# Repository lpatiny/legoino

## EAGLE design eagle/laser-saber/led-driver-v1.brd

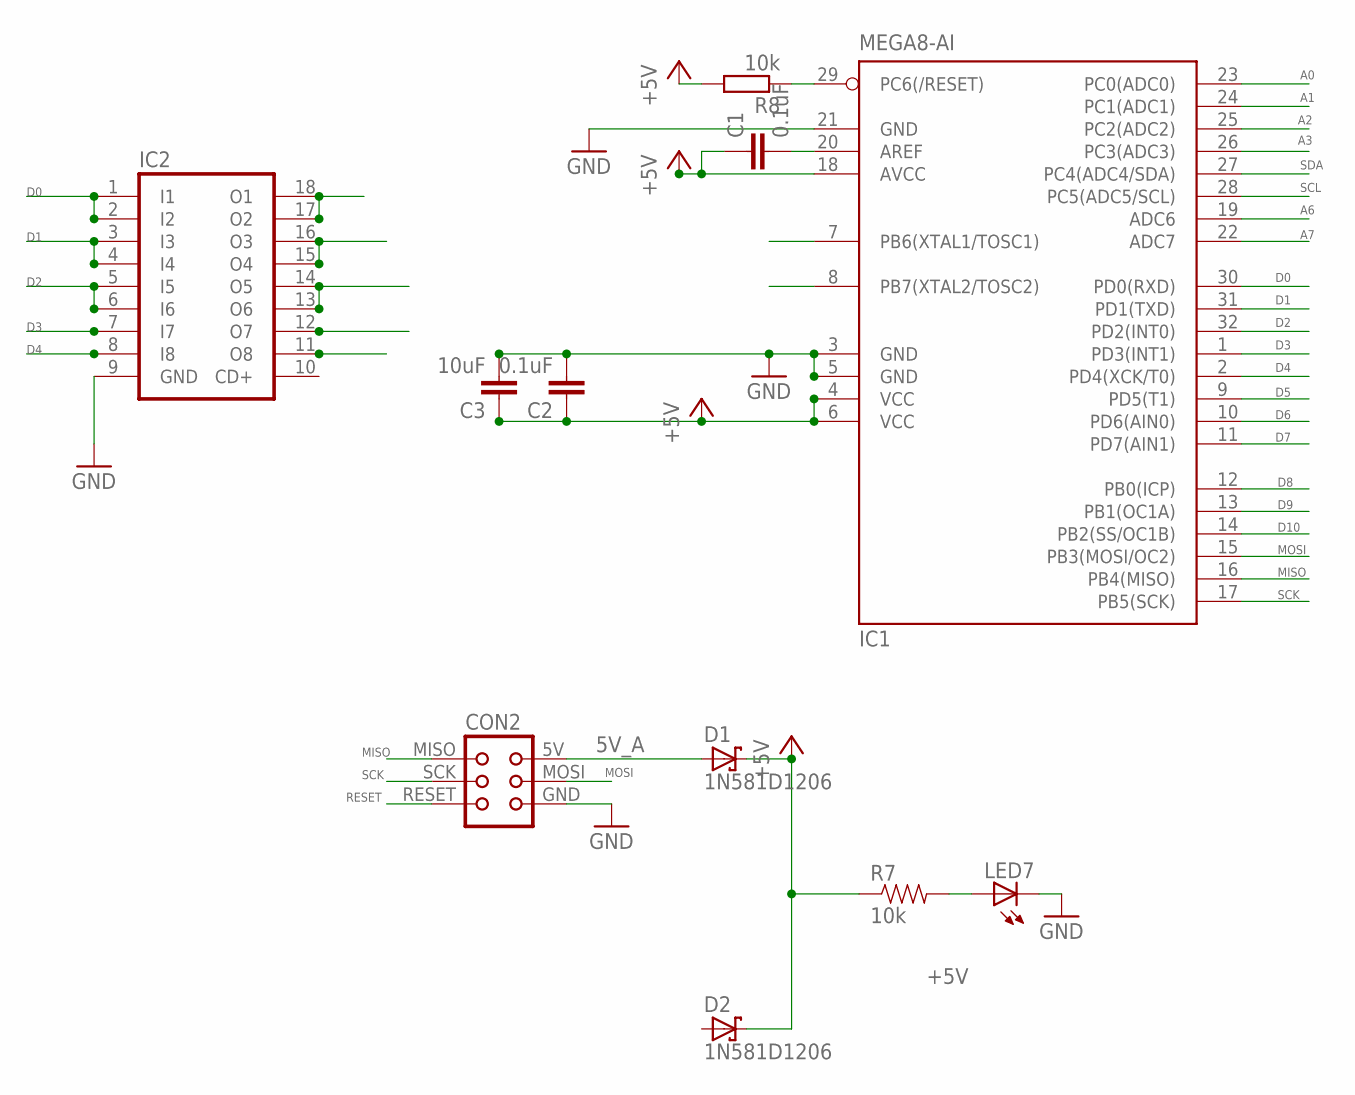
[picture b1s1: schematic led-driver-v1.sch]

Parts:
C1, C2: 0.1uF; C1206
C3: 10uF; C1206
CON2: TINYISPTAG; TC2030-MCP
D1, D2: 1N581D1206; LED-1206
IC1: MEGA8-AI; TQFP32-08
IC2: ULN2803A; SO18W
LED7: LEDCHIP-LED0603; CHIP-LED0603
R7: 10k; 0603-RES
R8: 10k; M1206

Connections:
5V_A: CON2.5V (VCC), D1.A
+5V: C1.1, C2.1, C3.1, D1.C, D2.C, IC1.4 (VCC), IC1.6 (VCC), IC1.18 (AVCC), R7.1, R8.2
A0: IC1.23 (PC0(ADC0))
A1: IC1.24 (PC1(ADC1))
A2: IC1.25 (PC2(ADC2))
A3: IC1.26 (PC3(ADC3))
A6: IC1.19 (ADC6)
A7: IC1.22 (ADC7)
D0: IC1.30 (PD0(RXD)), IC2.1 (I1), IC2.2 (I2)
D1: IC1.31 (PD1(TXD)), IC2.3 (I3), IC2.4 (I4)
D2: IC1.32 (PD2(INT0)), IC2.5 (I5), IC2.6 (I6)
D3: IC1.1 (PD3(INT1)), IC2.7 (I7)
D4: IC1.2 (PD4(XCK/T0)), IC2.8 (I8)
D5: IC1.9 (PD5(T1))
D6: IC1.10 (PD6(AIN0))
D7: IC1.11 (PD7(AIN1))
D8: IC1.12 (PB0(ICP))
D9: IC1.13 (PB1(OC1A))
D10: IC1.14 (PB2(SS/OC1B))
GND: C2.2, C3.2, CON2.GND, IC1.3 (GND), IC1.5 (GND), IC1.21 (GND), IC2.9 (GND), LED7.C
MISO: CON2.MISO, IC1.16 (PB4(MISO))
MOSI: CON2.MOSI, IC1.15 (PB3(MOSI/OC2))
unnamed: IC2.17 (O2), IC2.18 (O1)
unnamed: C1.2, IC1.20 (AREF)
unnamed: IC2.15 (O4), IC2.16 (O3)
unnamed: IC2.13 (O6), IC2.14 (O5)
unnamed: LED7.A, R7.2
PB6: IC1.7 (PB6(XTAL1/TOSC1))
PB7: IC1.8 (PB7(XTAL2/TOSC2))
RESET: CON2.RESET, IC1.29 (PC6(/RESET)), R8.1
SCK: CON2.SCK, IC1.17 (PB5(SCK))
SCL: IC1.28 (PC5(ADC5/SCL))
SDA: IC1.27 (PC4(ADC4/SDA))

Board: 2 copper layers, 11 parts (0 on the bottom side), 17 nets, no tracks yet.

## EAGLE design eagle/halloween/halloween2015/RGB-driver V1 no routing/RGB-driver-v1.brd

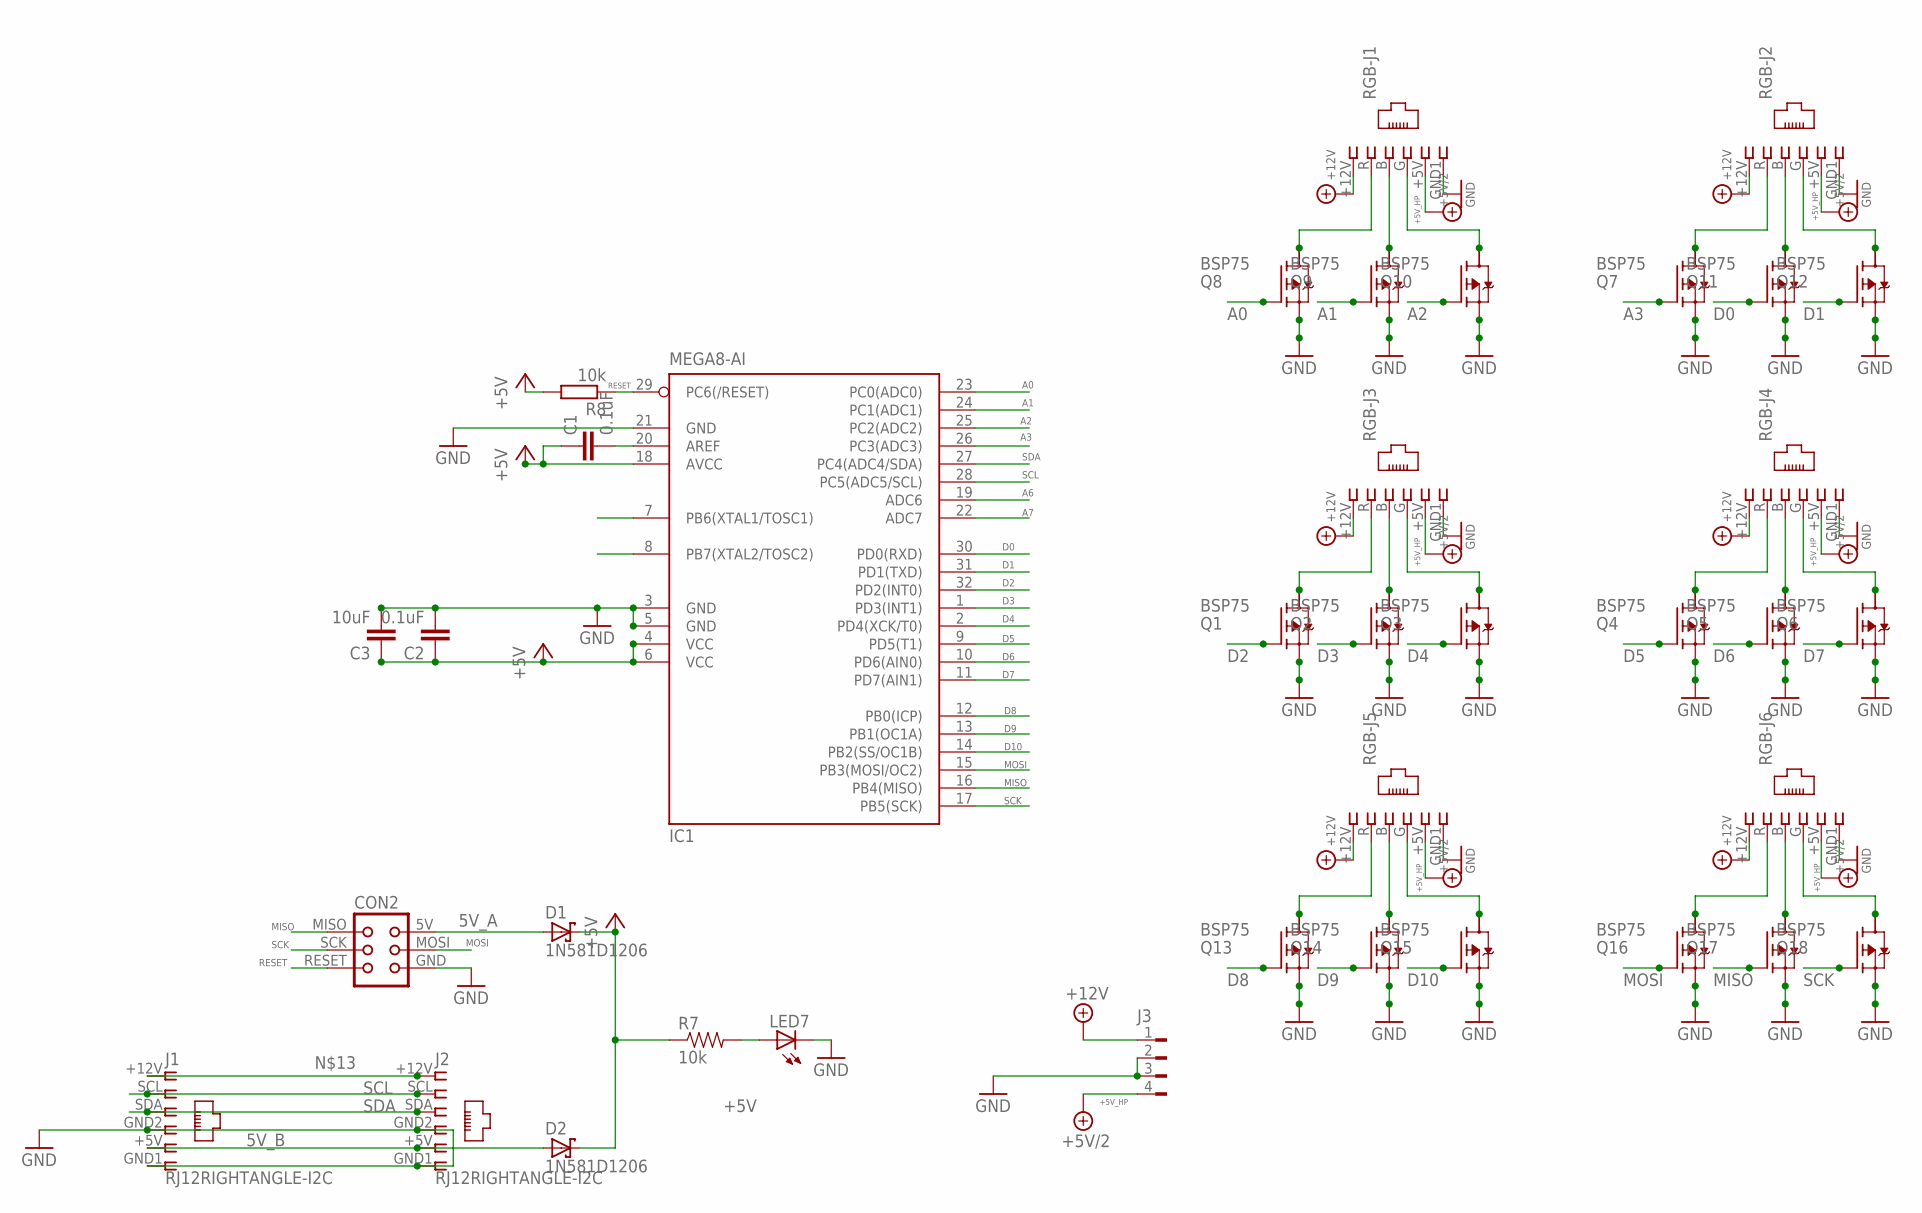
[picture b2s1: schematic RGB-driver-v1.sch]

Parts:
C1, C2: 0.1uF; C1206
C3: 10uF; C1206
CON2: TINYISPTAG; TC2030-MCP
D1, D2: 1N581D1206; LED-1206
IC1: MEGA8-AI; TQFP32-08
J1, J2: RJ12RIGHTANGLE-I2C; RJ12-RIGHTANGLE-I2C
J3: FLOP-4W827001; 827001
LED7: LEDCHIP-LED0603; CHIP-LED0603
Q1, Q2, Q3, Q4, Q5, Q6, Q7, Q8, Q9, Q10, Q11, Q12, Q13, Q14, Q15, Q16, Q17, Q18: BSP75; PG-SOT-223
R7: 10k; 0603-RES
R8: 10k; M1206
RGB-J1, RGB-J2, RGB-J3, RGB-J4, RGB-J5, RGB-J6: RJ12; RJ12-STRAIGHT-RGB

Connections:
5V_A: CON2.5V (VCC), D1.A
5V_B: D2.A, J1.+5V (5), J2.+5V (5)
+5V: C1.1, C2.1, C3.1, D1.C, D2.C, IC1.4 (VCC), IC1.6 (VCC), IC1.18 (AVCC), R7.1, R8.2
+5V_HP: J3.4, RGB-J1.+5V (5), RGB-J2.+5V (5), RGB-J3.+5V (5), RGB-J4.+5V (5), RGB-J5.+5V (5), RGB-J6.+5V (5)
+12V_HP: J3.1, RGB-J1.+12V (1), RGB-J2.+12V (1), RGB-J3.+12V (1), RGB-J4.+12V (1), RGB-J5.+12V (1), RGB-J6.+12V (1)
A0: IC1.23 (PC0(ADC0)), Q8.1 (G)
A1: IC1.24 (PC1(ADC1)), Q9.1 (G)
A2: IC1.25 (PC2(ADC2)), Q10.1 (G)
A3: IC1.26 (PC3(ADC3)), Q7.1 (G)
A6: IC1.19 (ADC6)
A7: IC1.22 (ADC7)
D0: IC1.30 (PD0(RXD)), Q11.1 (G)
D1: IC1.31 (PD1(TXD)), Q12.1 (G)
D2: IC1.32 (PD2(INT0)), Q1.1 (G)
D3: IC1.1 (PD3(INT1)), Q2.1 (G)
D4: IC1.2 (PD4(XCK/T0)), Q3.1 (G)
D5: IC1.9 (PD5(T1)), Q4.1 (G)
D6: IC1.10 (PD6(AIN0)), Q5.1 (G)
D7: IC1.11 (PD7(AIN1)), Q6.1 (G)
D8: IC1.12 (PB0(ICP)), Q13.1 (G)
D9: IC1.13 (PB1(OC1A)), Q14.1 (G)
D10: IC1.14 (PB2(SS/OC1B)), Q15.1 (G)
GND: C2.2, C3.2, CON2.GND, IC1.3 (GND), IC1.5 (GND), IC1.21 (GND), J1.GND1 (6), J1.GND2 (4), J2.GND1 (6), J2.GND2 (4), J3.2, J3.3, LED7.C, Q1.3 (S), Q2.3 (S), Q3.3 (S), Q4.3 (S), Q5.3 (S), Q6.3 (S), Q7.3 (S), Q8.3 (S), Q9.3 (S), Q10.3 (S), Q11.3 (S), Q12.3 (S), Q13.3 (S), Q14.3 (S), Q15.3 (S), Q16.3 (S), Q17.3 (S), Q18.3 (S), RGB-J1.GND1 (6), RGB-J2.GND1 (6), RGB-J3.GND1 (6), RGB-J4.GND1 (6), RGB-J5.GND1 (6), RGB-J6.GND1 (6)
MISO: CON2.MISO, IC1.16 (PB4(MISO)), Q17.1 (G)
MOSI: CON2.MOSI, IC1.15 (PB3(MOSI/OC2)), Q16.1 (G)
unnamed: Q2.2 (D), RGB-J3.B (3)
unnamed: Q1.2 (D), RGB-J3.R (2)
unnamed: Q3.2 (D), RGB-J3.G (4)
unnamed: C1.2, IC1.20 (AREF)
unnamed: Q5.2 (D), RGB-J4.B (3)
unnamed: Q10.2 (D), RGB-J1.G (4)
unnamed: Q4.2 (D), RGB-J4.R (2)
unnamed: Q6.2 (D), RGB-J4.G (4)
unnamed: Q14.2 (D), RGB-J5.B (3)
unnamed: Q11.2 (D), RGB-J2.B (3)
unnamed: Q13.2 (D), RGB-J5.R (2)
unnamed: Q15.2 (D), RGB-J5.G (4)
unnamed: J1.+12V (1), J2.+12V (1)
unnamed: Q17.2 (D), RGB-J6.B (3)
unnamed: LED7.A, R7.2
unnamed: Q16.2 (D), RGB-J6.R (2)
unnamed: Q18.2 (D), RGB-J6.G (4)
unnamed: Q7.2 (D), RGB-J2.R (2)
unnamed: Q12.2 (D), RGB-J2.G (4)
unnamed: Q9.2 (D), RGB-J1.B (3)
unnamed: Q8.2 (D), RGB-J1.R (2)
PB6: IC1.7 (PB6(XTAL1/TOSC1))
PB7: IC1.8 (PB7(XTAL2/TOSC2))
RESET: CON2.RESET, IC1.29 (PC6(/RESET)), R8.1
SCK: CON2.SCK, IC1.17 (PB5(SCK)), Q18.1 (G)
SCL: IC1.28 (PC5(ADC5/SCL)), J1.SCL (2), J2.SCL (2)
SDA: IC1.27 (PC4(ADC4/SDA)), J1.SDA (3), J2.SDA (3)

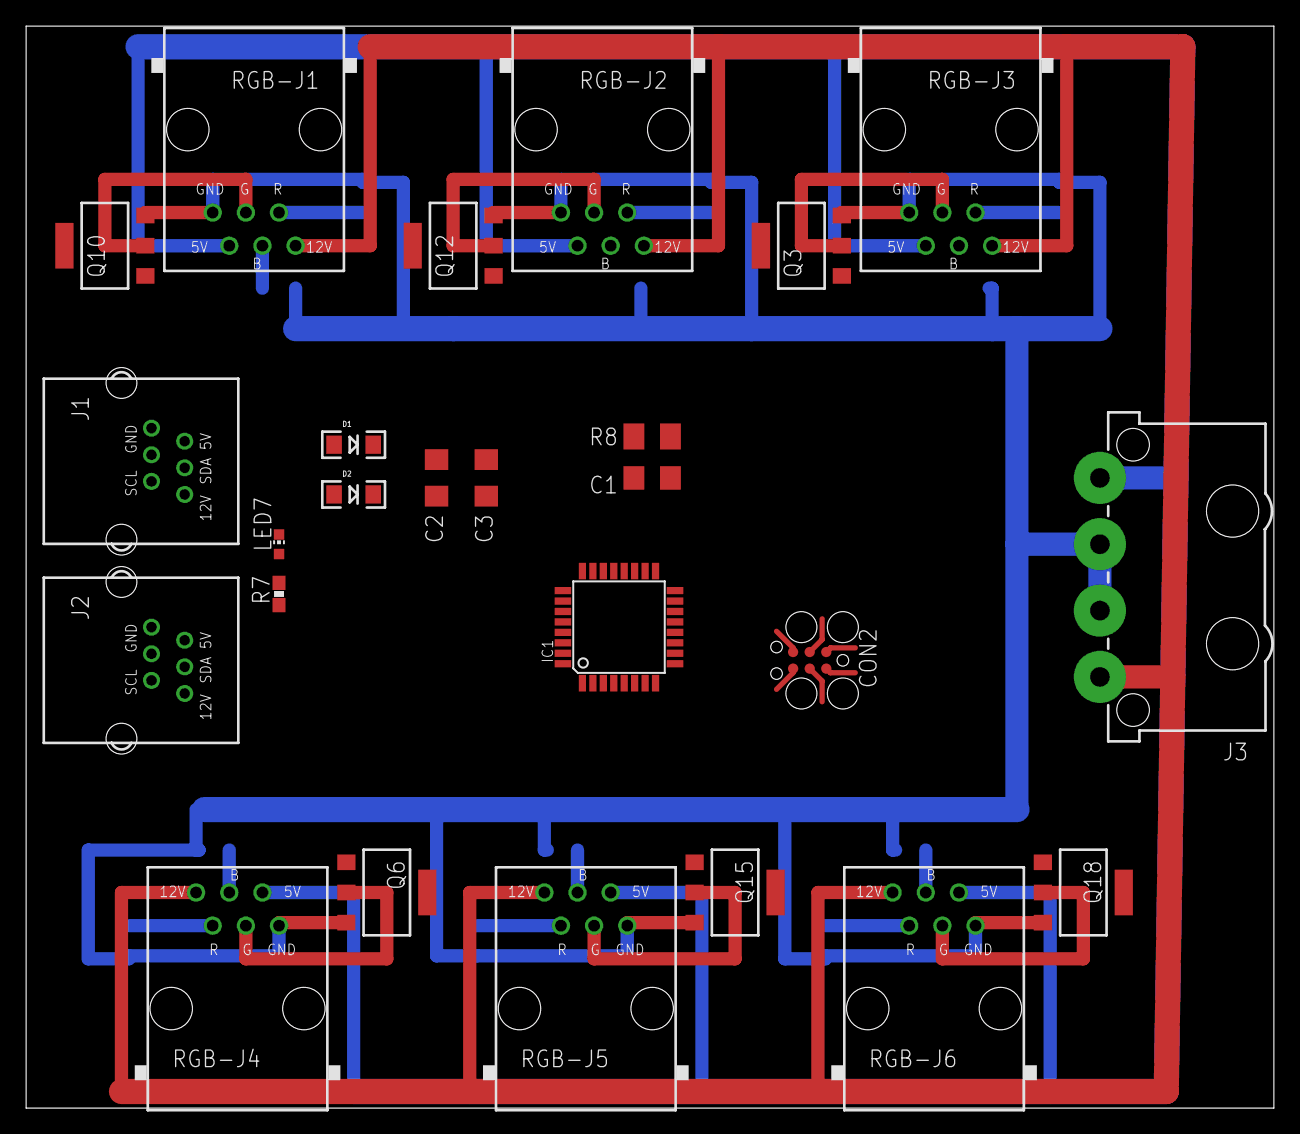
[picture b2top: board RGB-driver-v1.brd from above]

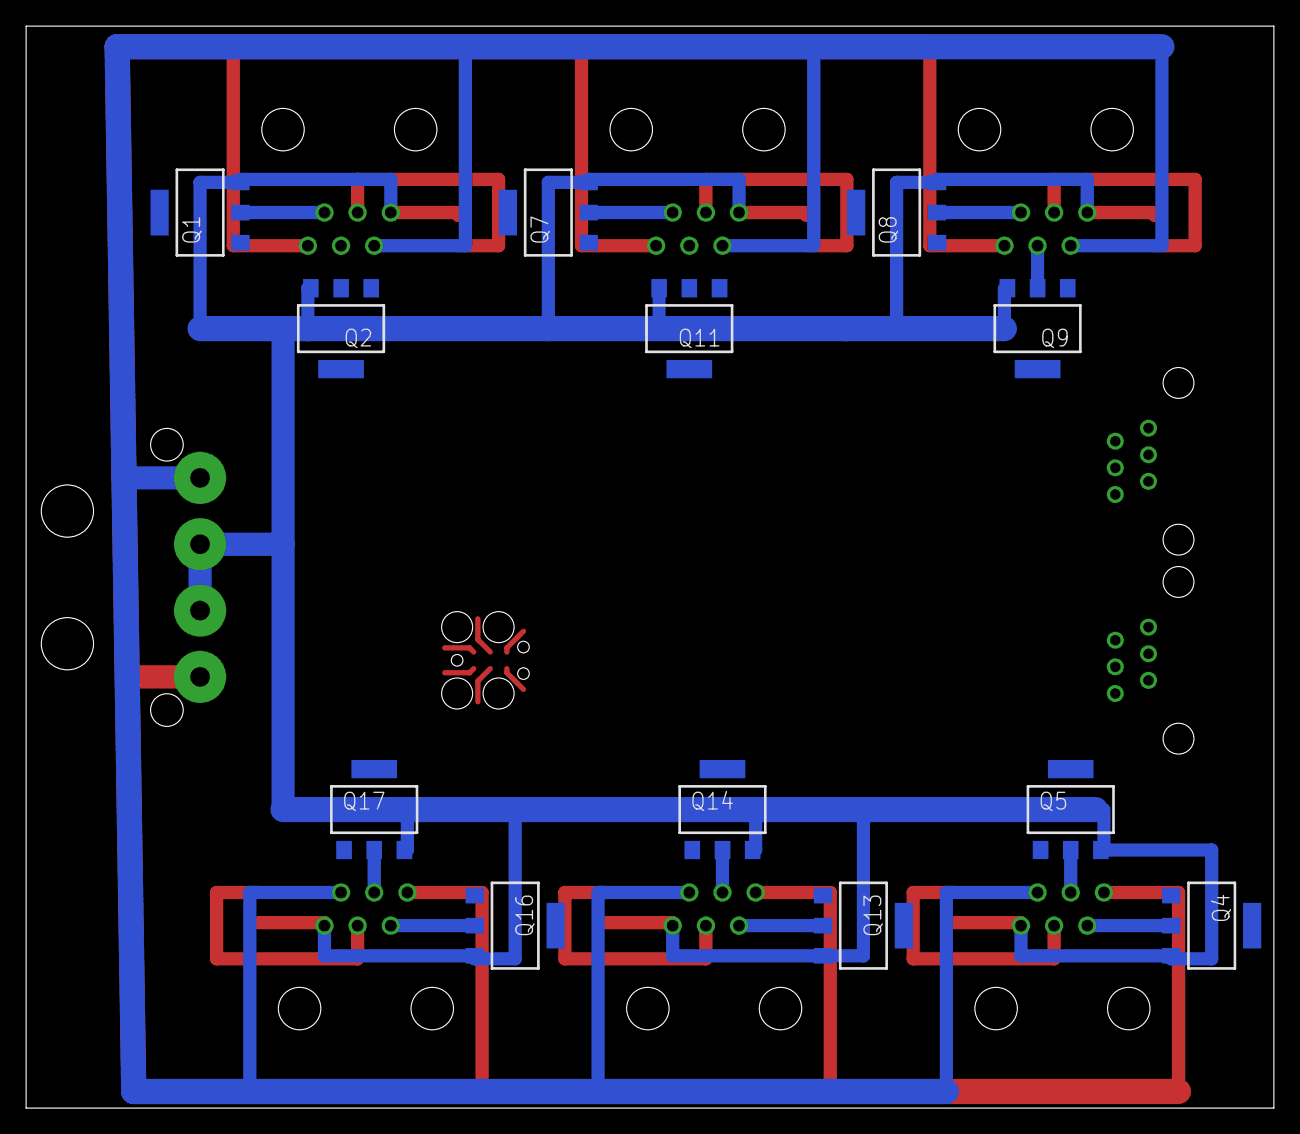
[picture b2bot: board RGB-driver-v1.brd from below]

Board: 2 copper layers, 95.6 x 82.9 mm, 37 parts (12 on the bottom side), 48 nets.

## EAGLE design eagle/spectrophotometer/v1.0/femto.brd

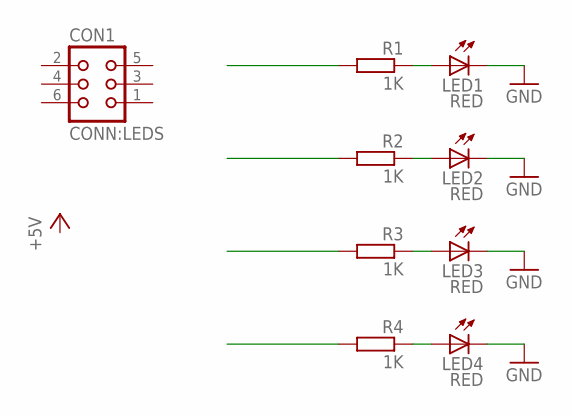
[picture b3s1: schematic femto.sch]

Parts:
CON1: CONN:LEDS; IDC-2*3
LED1, LED2, LED3, LED4: RED; CHIP-LED0805
R1, R2, R3, R4: 1K; R0805

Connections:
D13*: R1.2
D13*1: R2.2
D13*2: R3.2
D13*3: R4.2
GND: LED1.C, LED2.C, LED3.C, LED4.C
unnamed: LED1.A, R1.1
unnamed: LED2.A, R2.1
unnamed: LED3.A, R3.1
unnamed: LED4.A, R4.1

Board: 2 copper layers, 9 parts (0 on the bottom side), 5 nets, no tracks yet.

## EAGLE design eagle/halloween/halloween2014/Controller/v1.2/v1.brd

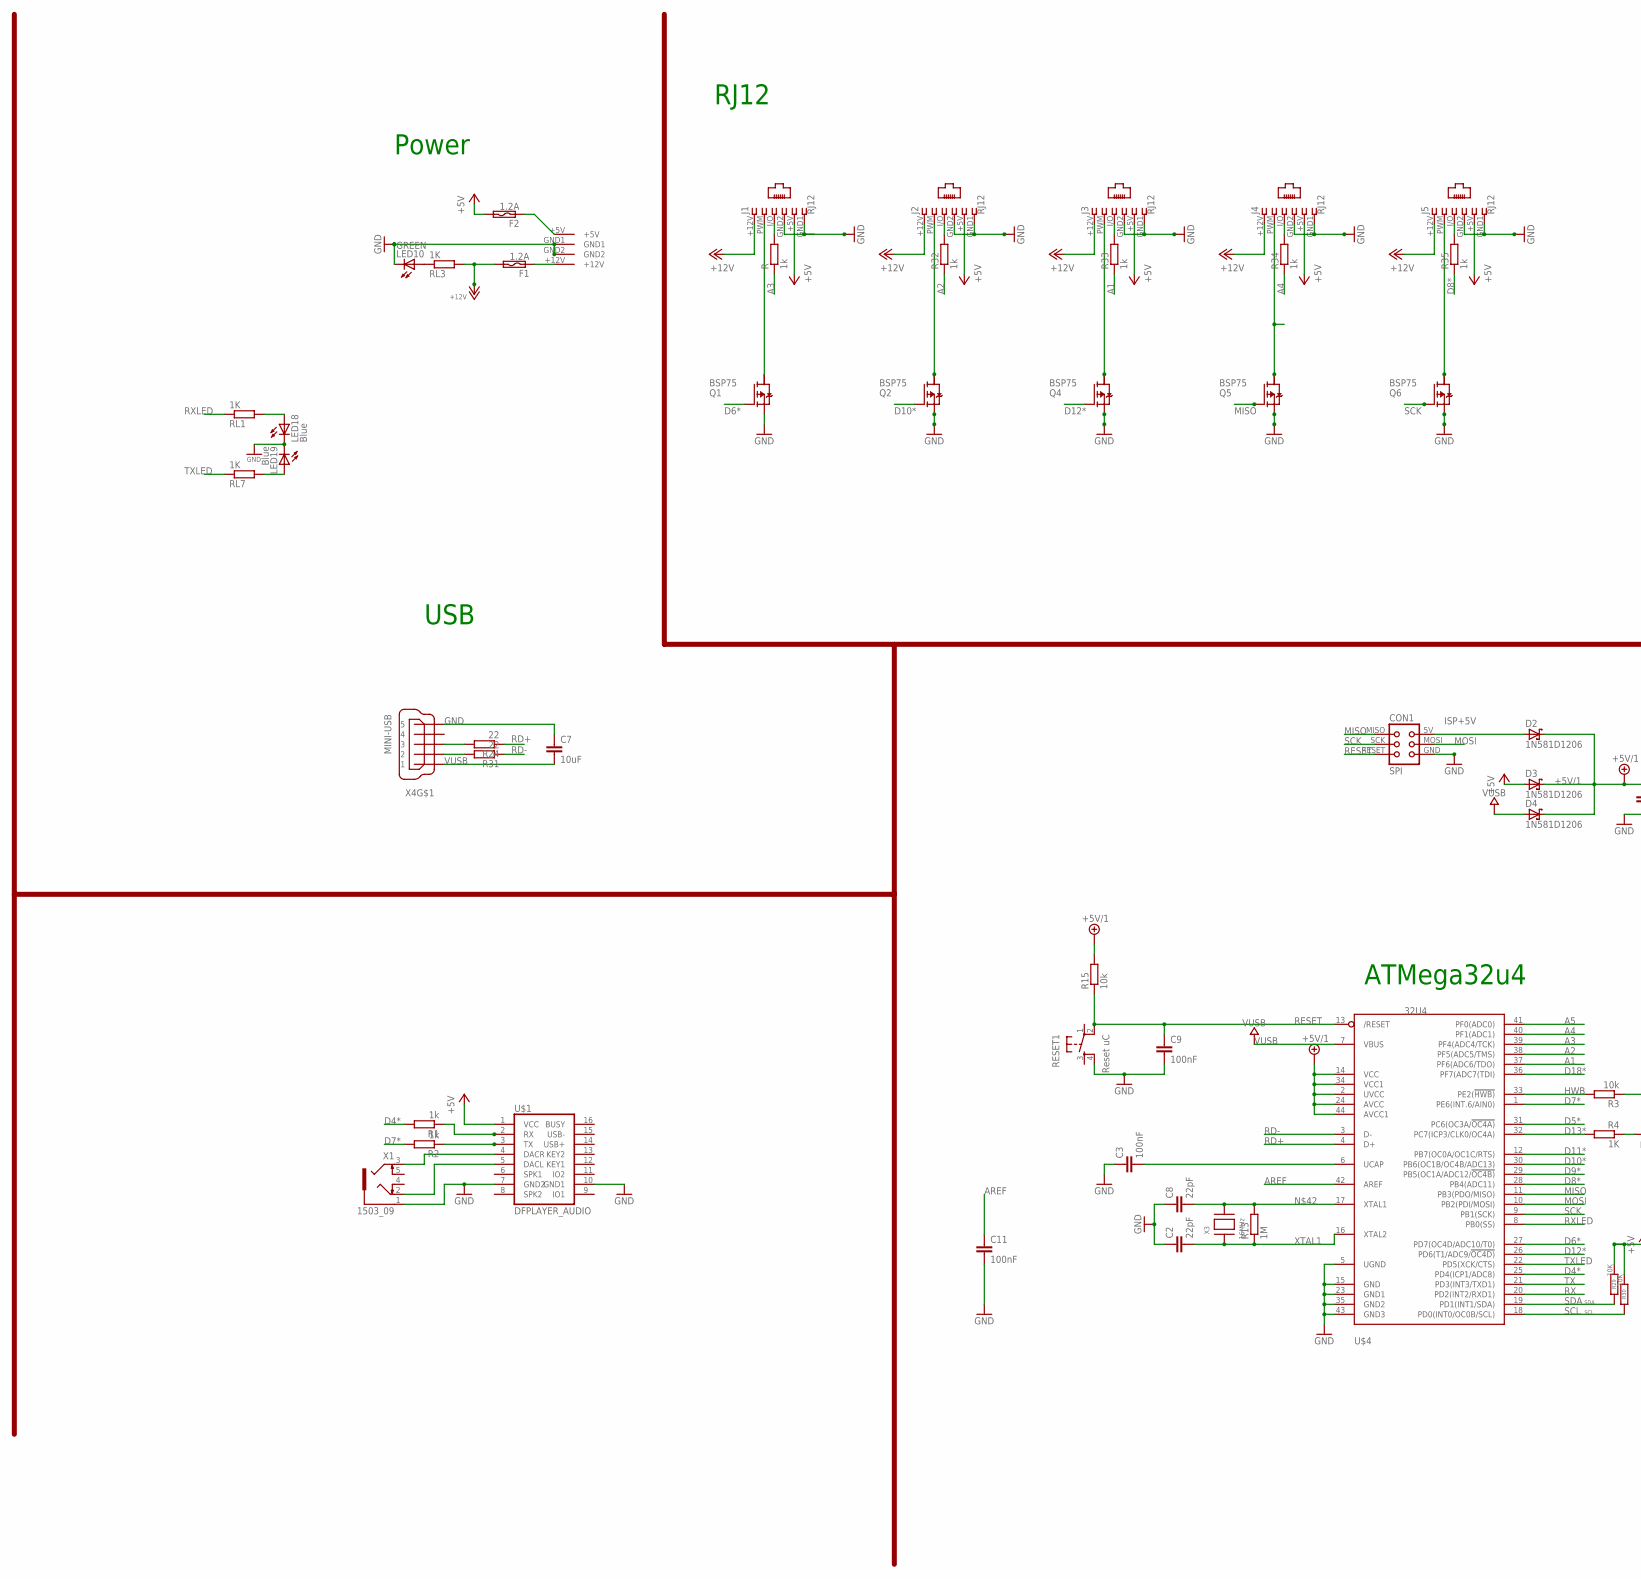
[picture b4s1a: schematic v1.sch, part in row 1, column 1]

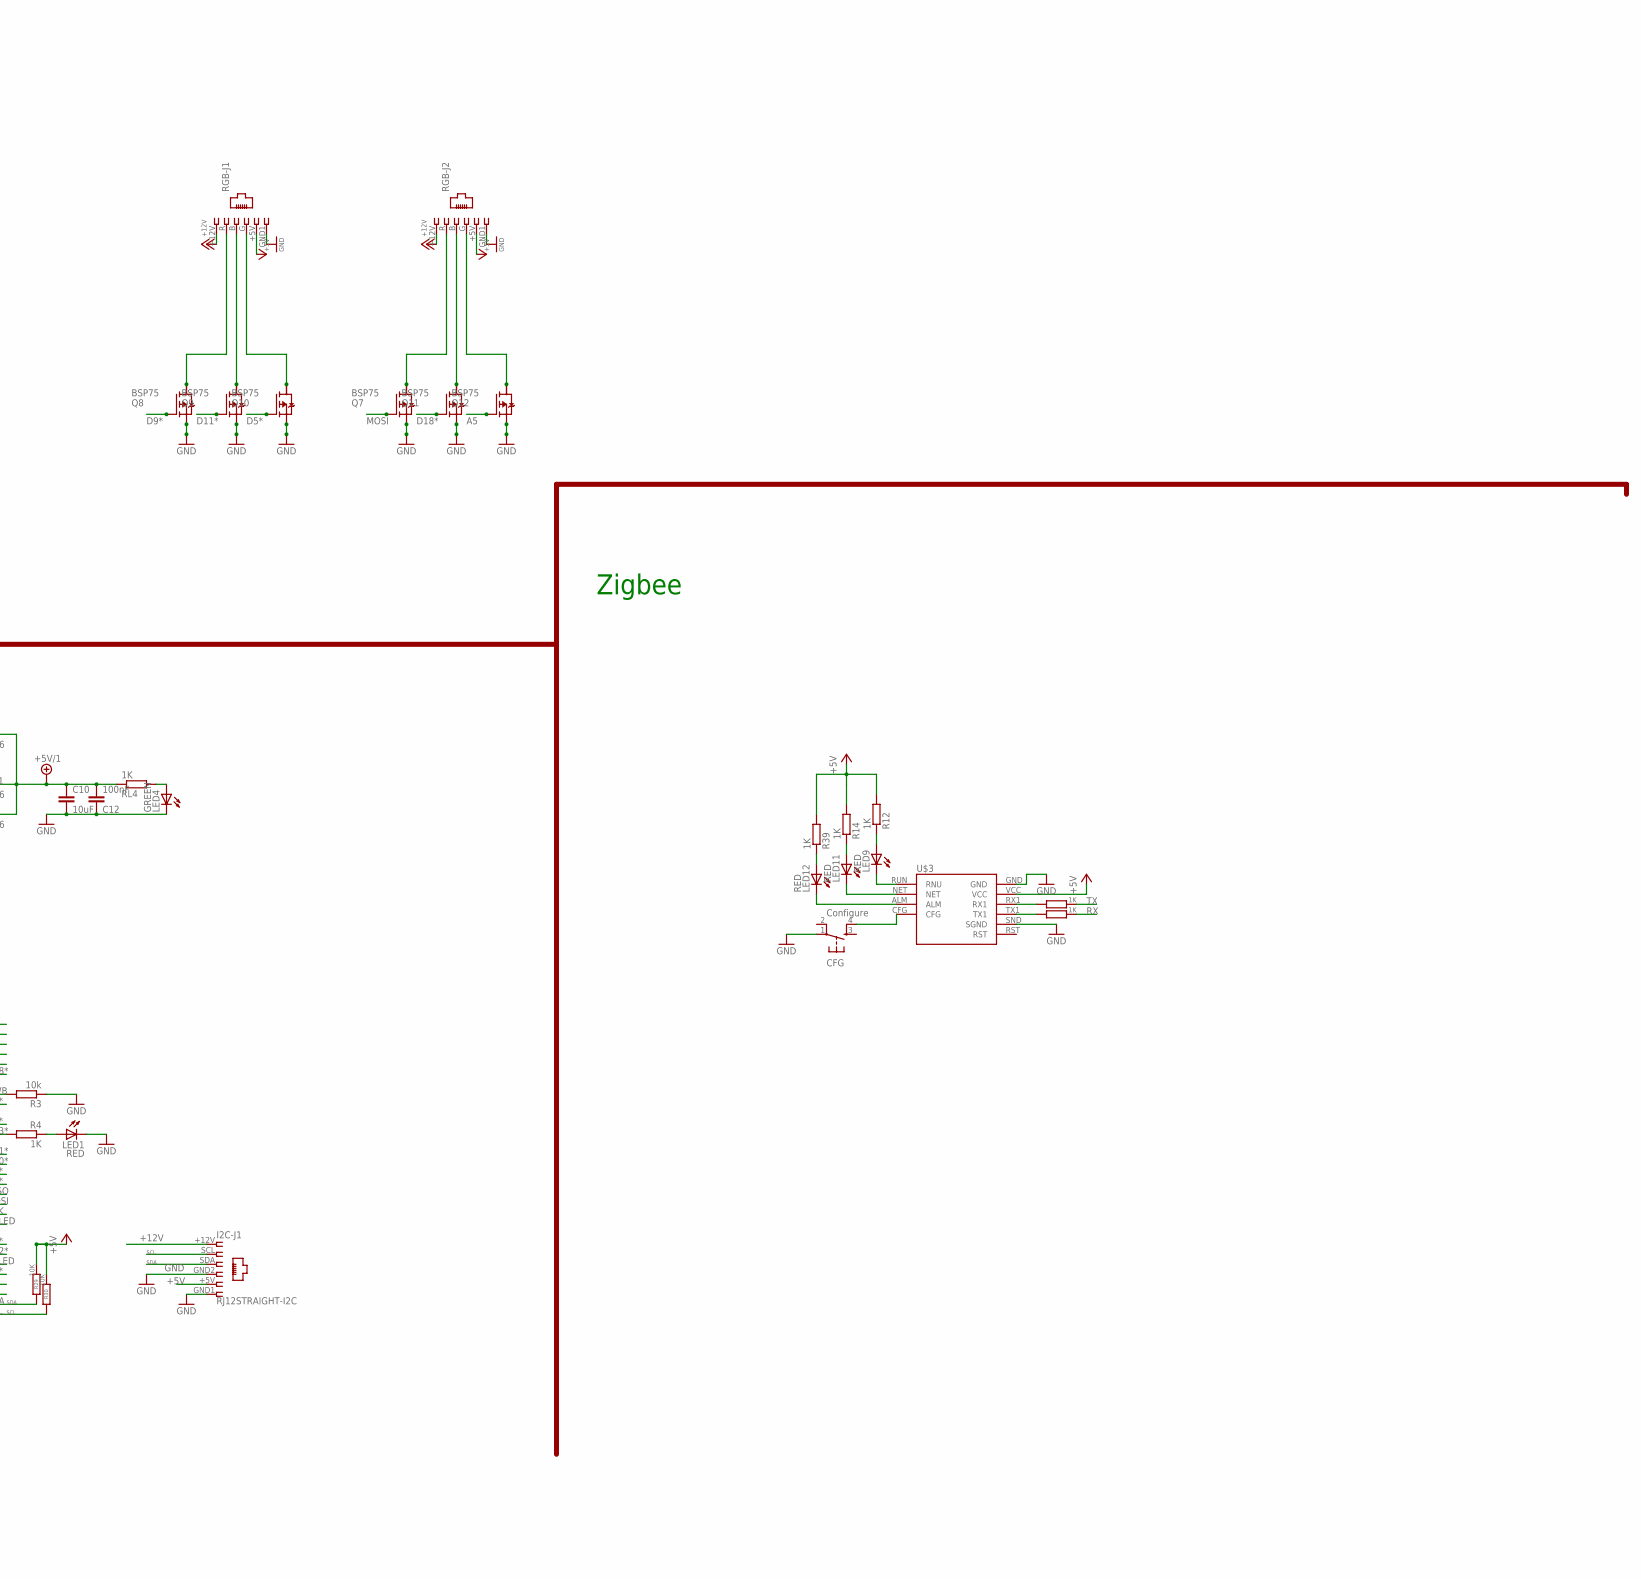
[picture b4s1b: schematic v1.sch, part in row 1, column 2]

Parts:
C2, C8: 22pF; C1206
C3, C9, C11, C12: 100nF; C1206
C7, C10: 10uF; C1206
CFG: Configure; TACTILE_SWITCH_SMD
CON1: SPI; TC2030-MCP-NL
D2, D3, D4: 1N581D1206; LED-1206
F1, F2: 1.2A; C1812
I2C-J1: RJ12STRAIGHT-I2C; RJ12-STRAIGHT-I2C
J1, J2, J3, J4, J5: RJ12; RJ12-STRAIGHT
LED1, LED9, LED11, LED12: RED; CHIP-LED0805
LED4, LED10: GREEN; CHIP-LED0805
LED18, LED19: Blue; CHIP-LED0805
Q1, Q2, Q4, Q5, Q6, Q7, Q8, Q9, Q10, Q11, Q12: BSP75; PG-SOT-223
R, R1, R2, R32, R33, R34, R35: 1k; R0805
R3, R15: 10k; M0805
R4, R8, R11, R12, R14, R39: 1K; R0805
R13: 1M; R1206
R24, R31: 22; M1206
R29, R30: 10K; M0805
RESET1: Reset uC; TACTILE_SWITCH_SMD
RGB-J1, RGB-J2: RJ12; RJ12-STRAIGHT-RGB
RL1, RL3, RL4, RL7: 1K; R0805
U$1: DFPLAYER_AUDIO; DIL16-7
U$3: SZ05-ZIGBEESMD; SZ05-ZIGBEE3
U$4: 32U4; TQFP44
U$6: KPJX-4S-S
X1: 1503_09
X3: 16MHz; NX6035
X4: MINI-USB; 32005-201

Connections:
+5V: D3.A, F2.2, I2C-J1.+5V (5), J1.+5V (5), J2.+5V (5), J3.+5V (5), J4.+5V (5), J5.+5V (5), R12.2, R14.2, R29.1, R30.1, R39.2, RGB-J1.+5V (5), RGB-J2.+5V (5), U$1.1 (VCC), U$3.VCC
+5V/1: C10.1, C12.2, D2.C, D3.C, D4.C, R15.2, RL4.1, U$4.2 (UVCC), U$4.14 (VCC), U$4.24 (AVCC), U$4.34 (VCC1), U$4.44 (AVCC1)
+12V: F1.2, I2C-J1.+12V (1), J1.+12V (1), J2.+12V (1), J3.+12V (1), J4.+12V (1), J5.+12V (1), RGB-J1.+12V (1), RGB-J2.+12V (1), RL3.2
A1: R33.1, U$4.37 (PF6(ADC6/TDO))
A2: R32.1, U$4.38 (PF5(ADC5/TMS))
A3: R.1, U$4.39 (PF4(ADC4/TCK))
A4: R34.1, U$4.40 (PF1(ADC1))
A5: Q12.1 (G), U$4.41 (PF0(ADC0))
AREF: C11.1, U$4.42 (AREF)
D4*: R1.2, U$4.25 (PD4(ICP1/ADC8))
D5*: Q10.1 (G), U$4.31 (PC6(OC3A/!OC4A))
D6*: Q1.1 (G), U$4.27 (PD7(OC4D/ADC10/T0))
D7*: R2.2, U$4.1 (PE6(INT.6/AIN0))
D8*: R35.1, U$4.28 (PB4(ADC11))
D9*: Q8.1 (G), U$4.29 (PB5(OC1A/ADC12/!OC4B))
D10*: Q2.1 (G), U$4.30 (PB6(OC1B/OC4B/ADC13))
D11*: Q9.1 (G), U$4.12 (PB7(OC0A/OC1C/RTS))
D12*: Q4.1 (G), U$4.26 (PD6(T1/ADC9/!OC4D))
D13*: R4.2, U$4.32 (PC7(ICP3/CLK0/OC4A))
D18*: Q11.1 (G), U$4.36 (PF7(ADC7(TDI))
D+USB: R24.2, X4.3
D-USB: R31.2, X4.2
GND: C2.1, C3.1, C7.1, C8.1, C9.2, C10.2, C11.2, C12.1, CFG.1, CON1.GND, I2C-J1.GND1 (6), I2C-J1.GND2 (4), J1.GND1 (6), J1.GND2 (4), J2.GND1 (6), J2.GND2 (4), J3.GND1 (6), J3.GND2 (4), J4.GND1 (6), J4.GND2 (4), J5.GND1 (6), J5.GND2 (4), LED1.C, LED4.C, LED10.C, LED18.C, LED19.C, Q1.3 (S), Q2.3 (S), Q4.3 (S), Q5.3 (S), Q6.3 (S), Q7.3 (S), Q8.3 (S), Q9.3 (S), Q10.3 (S), Q11.3 (S), Q12.3 (S), R3.1, RESET1.4, RGB-J1.GND1 (6), RGB-J2.GND1 (6), U$1.7 (GND2), U$1.10 (GND1), U$3.GND, U$3.SND (SGND), U$4.5 (UGND), U$4.15 (GND), U$4.23 (GND1), U$4.35 (GND2), U$4.43 (GND3), U$6.GND1, U$6.GND2, X1.1, X4.5
GND1: LED9.C, U$3.RUN (RNU)
GND2: LED11.C, U$3.NET
GND3: LED12.C, U$3.ALM
HWB: R3.2, U$4.33 (PE2(!HWB))
ISP+5V: CON1.5V (VCC), D2.A
MISO: CON1.MISO, Q5.1 (G), U$4.11 (PB3(PDO/MISO))
MOSI: CON1.MOSI, Q7.1 (G), U$4.10 (PB2(PDI/MOSI))
unnamed: J3.PWM (2), Q4.2 (D)
unnamed: J2.I/O (3), R32.2
unnamed: R1.1, U$1.2 (RX)
unnamed: LED1.A, R4.1
unnamed: J4.PWM (2), Q5.2 (D)
unnamed: Q10.2 (D), RGB-J1.G (4)
unnamed: J3.I/O (3), R33.2
unnamed: LED18.A, RL1.2
unnamed: U$1.5 (DACL), X1.2
unnamed: Q11.2 (D), RGB-J2.B (3)
unnamed: R11.2, U$3.RX1
unnamed: LED4.A, RL4.2
unnamed: R2.1, U$1.3 (TX)
unnamed: LED19.A, RL7.2
unnamed: U$1.4 (DACR), X1.3
unnamed: C3.2, U$4.6 (UCAP)
unnamed: J1.I/O (3), R.2
unnamed: J5.PWM (2), Q6.2 (D)
unnamed: Q7.2 (D), RGB-J2.R (2)
unnamed: Q12.2 (D), RGB-J2.G (4)
unnamed: R8.2, U$3.TX1
unnamed: LED9.A, R12.1
unnamed: LED11.A, R14.1
unnamed: LED12.A, R39.1
unnamed: J2.PWM (2), Q2.2 (D)
unnamed: J4.I/O (3), R34.2
unnamed: J5.I/O (3), R35.2
unnamed: J1.PWM (2), Q1.2 (D)
unnamed: CFG.4, U$3.CFG
unnamed: F2.1, U$6.+5V
unnamed: F1.1, U$6.+12V
unnamed: C8.2, R13.2, U$4.17 (XTAL1), X3.P$2
unnamed: Q9.2 (D), RGB-J1.B (3)
unnamed: Q8.2 (D), RGB-J1.R (2)
unnamed: LED10.A, RL3.1
RD+: R24.1, U$4.4 (D+)
RD-: R31.1, U$4.3 (D-)
RESET: C9.1, CON1.RESET, R15.1, RESET1.2, U$4.13 (/RESET)
RX: R8.1, U$4.20 (PD2(INT2/RXD1))
RXLED: RL1.1, U$4.8 (PB0(SS))
SCK: CON1.SCK, Q6.1 (G), U$4.9 (PB1(SCK))
SCL: I2C-J1.SCL (2), R30.2, U$4.18 (PD0(INT0/OC0B/SCL))
SDA: I2C-J1.SDA (3), R29.2, U$4.19 (PD1(INT1/SDA))
TX: R11.1, U$4.21 (PD3(INT3/TXD1))
TXLED: RL7.1, U$4.22 (PD5(XCK/CTS))
VUSB: C7.2, D4.A, U$4.7 (VBUS), X4.1
XTAL1: C2.2, R13.1, U$4.16 (XTAL2), X3.P$1

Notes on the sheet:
RJ12
ATMega32u4
USB
Power
Zigbee

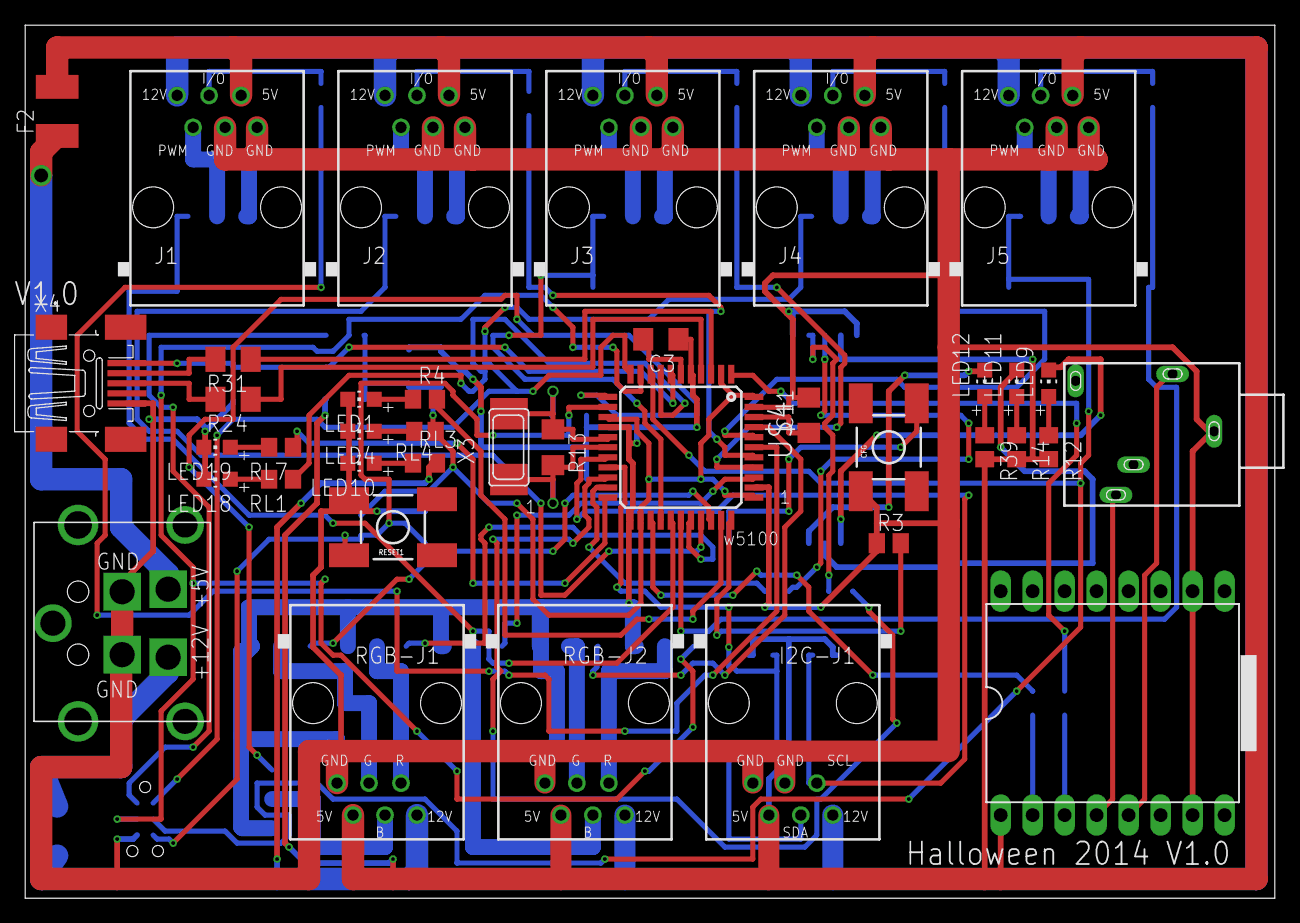
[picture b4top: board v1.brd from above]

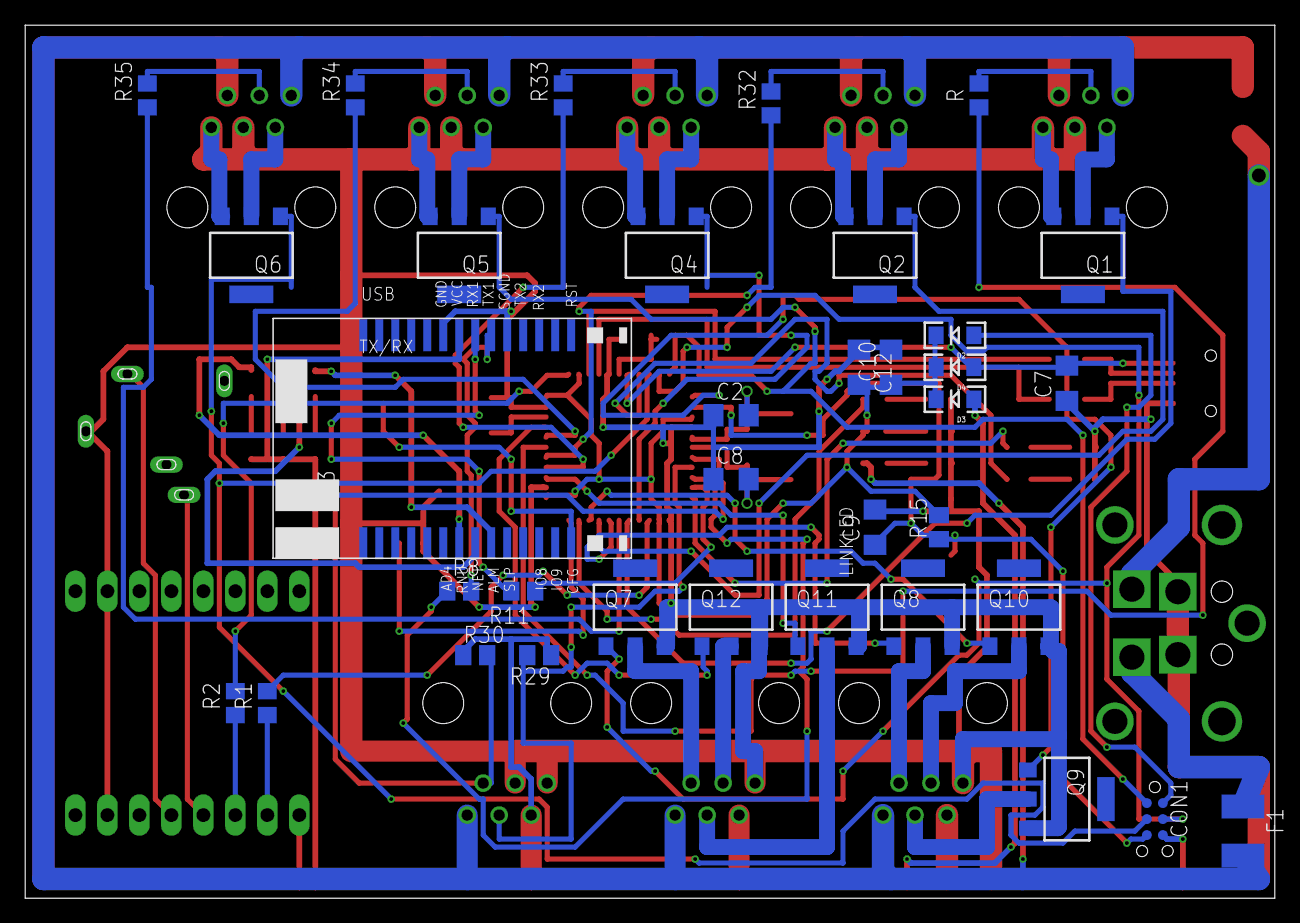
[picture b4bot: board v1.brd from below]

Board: 2 copper layers, 99.2 x 69.3 mm, 74 parts (35 on the bottom side), 77 nets.

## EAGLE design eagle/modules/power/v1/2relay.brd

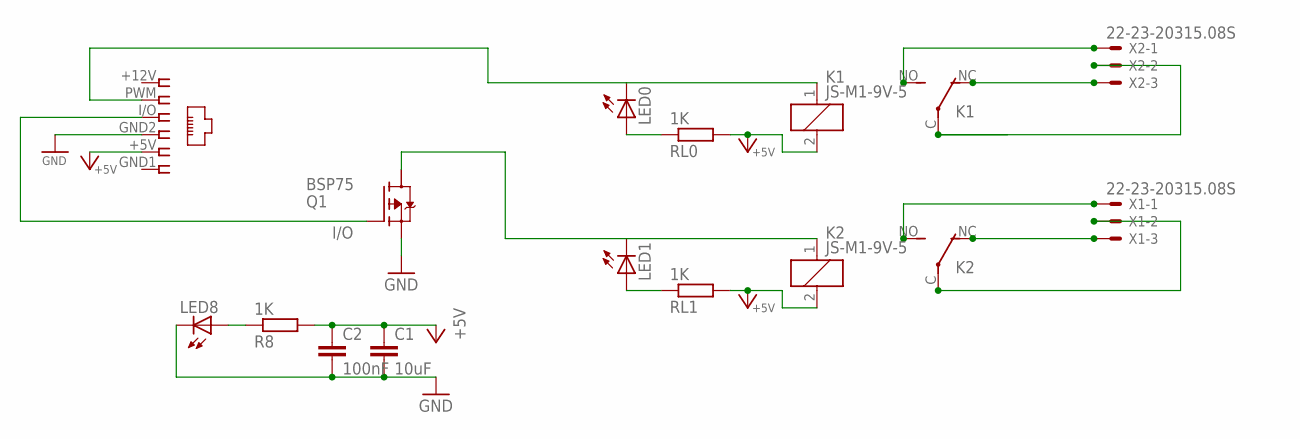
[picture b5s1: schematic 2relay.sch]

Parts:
C1: 10uF; C1206
C2: 100nF; C1206
I/O_PWM: I2C 1; RJ12-STRAIGHT
K1, K2: JS-M1-9V-5; JS-M
LED0, LED1, LED8: LED1206; LED-1206
Q1: BSP75; PG-SOT-223
R8: 1K; M1206
RL0, RL1: 1K; M1206
X1, X2: 22-23-20315.08S; 3-PIN-5.08S

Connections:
+5V: C1.1, C2.1, I/O_PWM.+5V (5), K1.2, K2.2, R8.2, RL0.2, RL1.2
GND: C1.2, C2.2, I/O_PWM.GND2 (4), LED8.C, Q1.3 (S)
I/O: I/O_PWM.I/O (3), Q1.1 (G)
unnamed: K2.1, LED1.C, Q1.2 (D)
unnamed: LED0.A, RL0.1
unnamed: LED1.A, RL1.1
unnamed: K2.C, X1.2
unnamed: K1.NC (O), X2.3
unnamed: K2.NC (O), X1.3
unnamed: K2.NO (S), X1.1
unnamed: K1.NO (S), X2.1
unnamed: LED8.A, R8.1
POWER1: K1.C, X2.2
PWM: I/O_PWM.PWM (2), K1.1, LED0.C

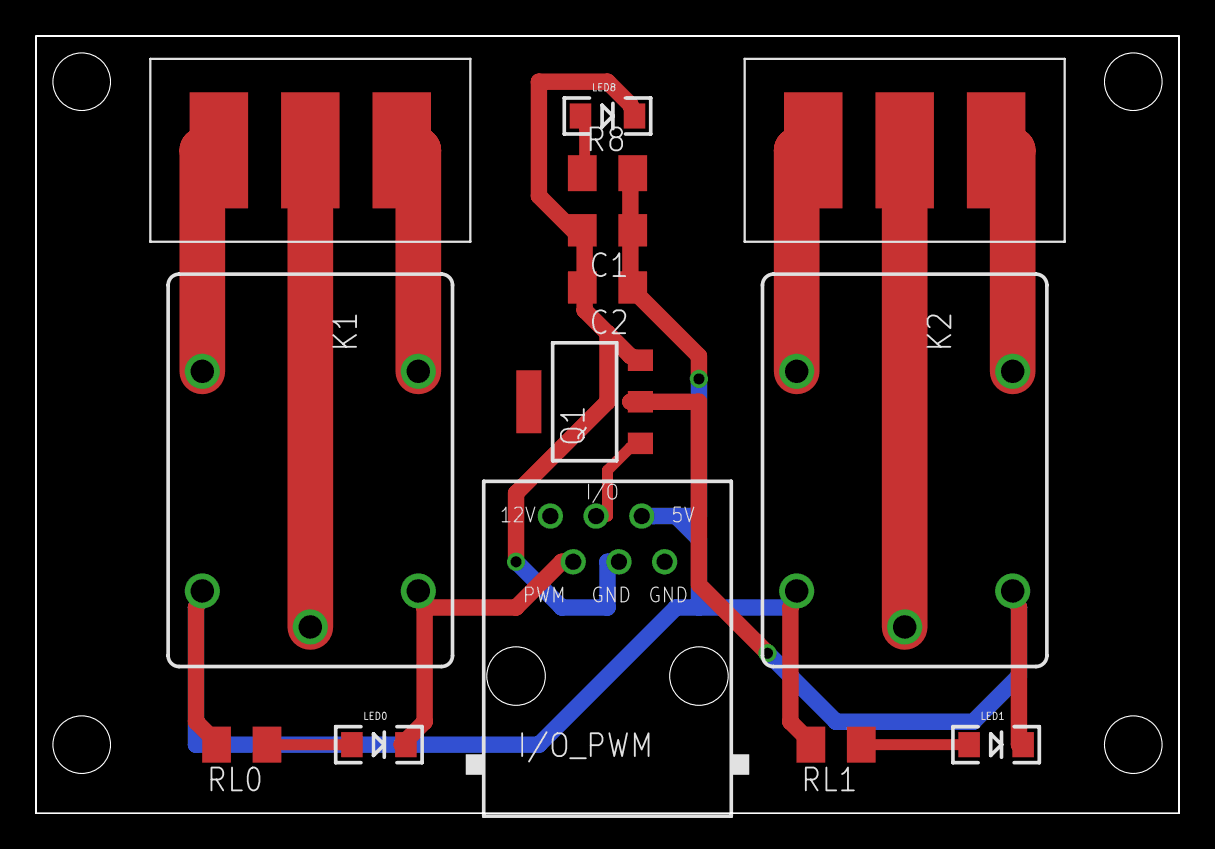
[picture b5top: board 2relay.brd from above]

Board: 2 copper layers, 63.5 x 43.2 mm, 14 parts (0 on the bottom side), 14 nets.

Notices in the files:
parts and their libraries:
lpatiny: ©2009 ROFA.cz - modified and updated by Robert Darlington ‹rdarlington@gmail.com›
SparkFun: Licensing: CC v3.0 Share-Alike You are welcome to use this library for commercial purposes.
